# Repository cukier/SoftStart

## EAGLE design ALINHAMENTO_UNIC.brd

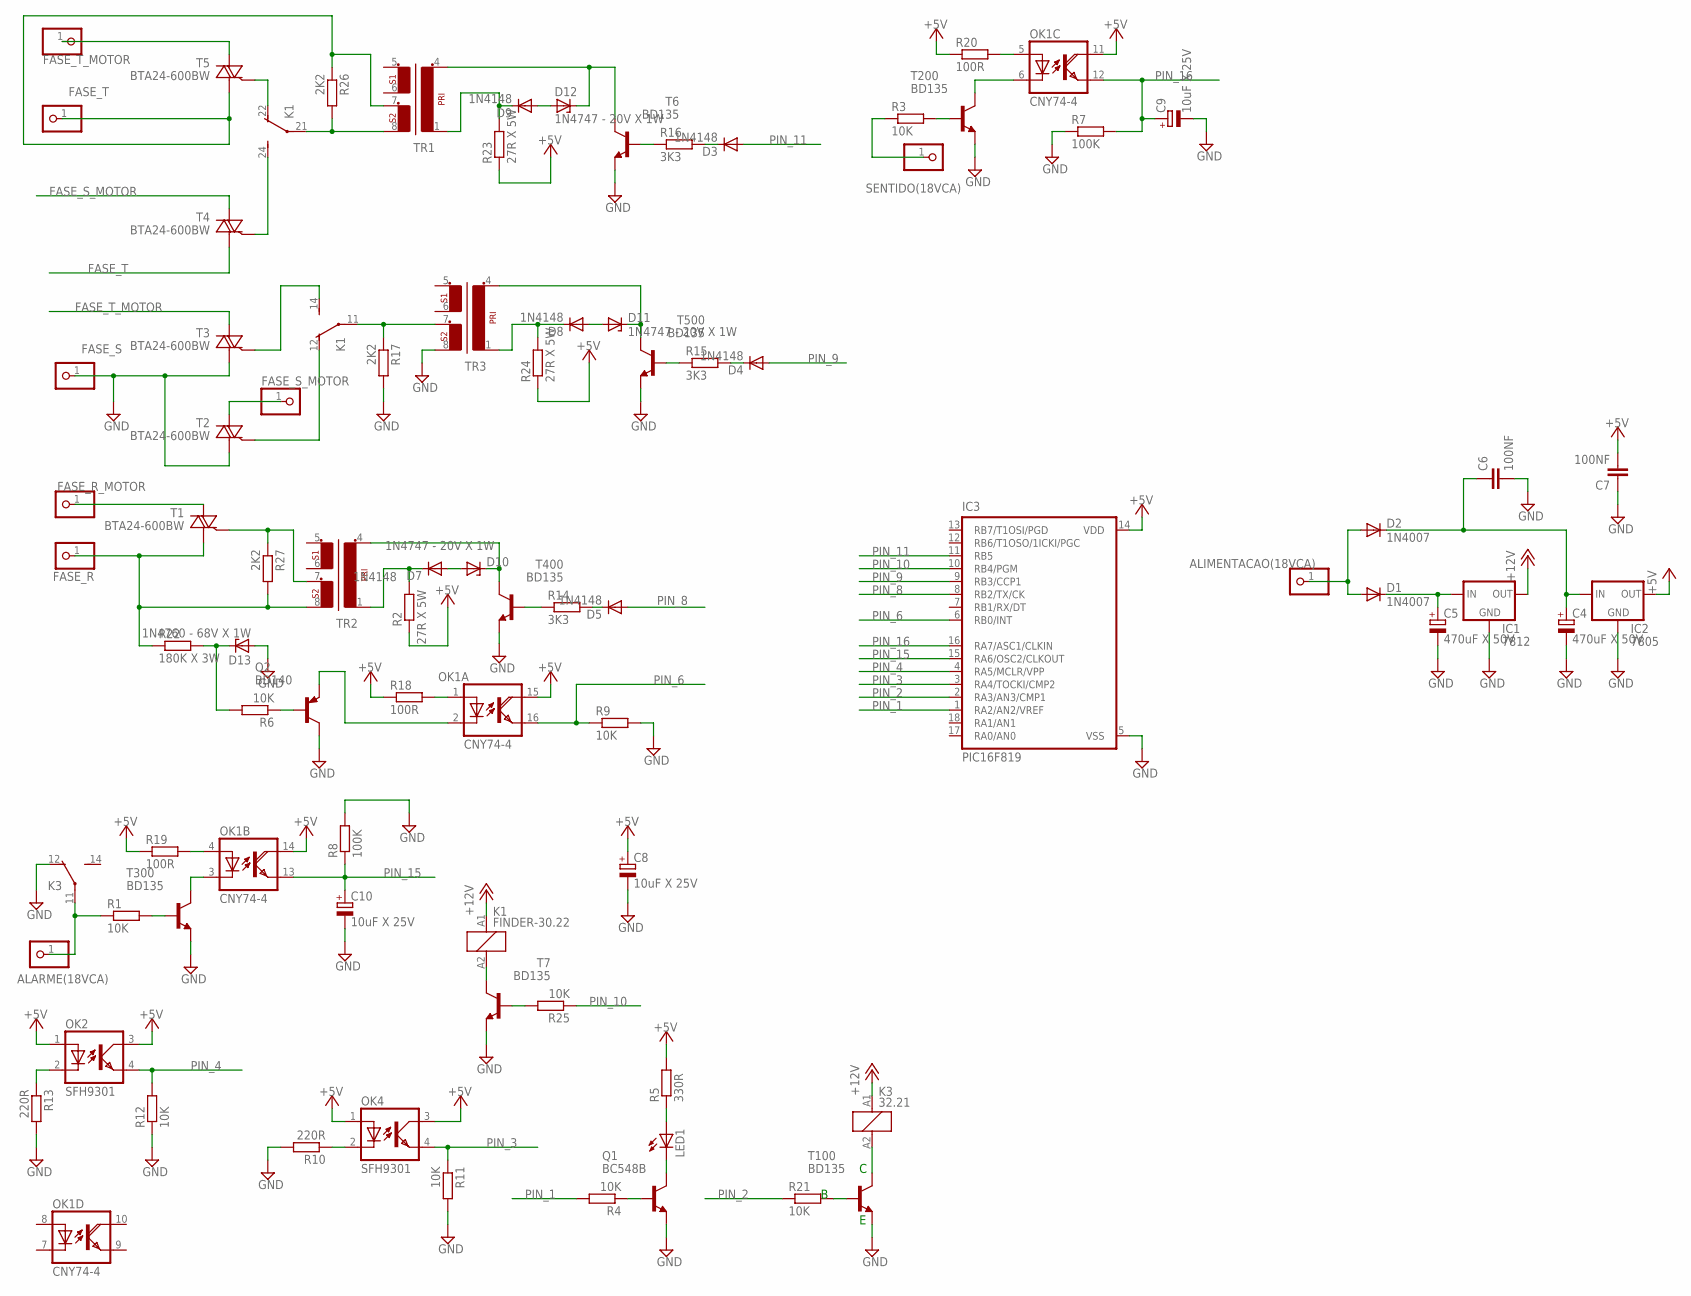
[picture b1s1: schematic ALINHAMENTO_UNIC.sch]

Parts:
ALARME(18VCA): PINHD-1X1; 1X01
ALIMENTACAO(18VCA): PINHD-1X1; 1X01
C4, C5: 470uF X 50V; E5-13
C6, C7: 100NF; C050-025X075
C8, C9, C10: 10uF X 25V; E2-5
D1, D2: 1N4007; DO41-10
D3, D4, D5, D7, D8, D9: 1N4148; DO35-10
D10, D11, D12: 1N4747 - 20V X 1W; DO41Z10
D13: 1N4760 - 68V X 1W; DO41Z10
FASE_R: PINHD-1X1; 1X01
FASE_R_MOTOR: PINHD-1X1; 1X01
FASE_S: PINHD-1X1; 1X01
FASE_S_MOTOR: PINHD-1X1; 1X01
FASE_T: PINHD-1X1; 1X01
FASE_T_MOTOR: PINHD-1X1; 1X01
IC1: 7812; 78MXXS
IC2: 7805; 78MXXS
IC3: PIC16F819; DIL18
K1: FINDER-30.22
K3: 32.21; RP51
LED1: LED5MM
OK1: CNY74-4; DIL16
OK2, OK4: SFH9301
Q1: BC548B; TO92-EBC
Q2: BD140; TO126
R1, R3, R4, R6, R9, R11, R12, R21, R25: 10K; 0207/10
R2, R23, R24: 27R X 5W; 0617/22
R5: 330R; 0207/10
R7, R8: 100K; 0207/10
R10, R13: 220R; 0207/10
R14, R15, R16: 3K3; 0207/10
R17, R26, R27: 2K2; 0207/10
R18, R19, R20: 100R; 0207/10
R22: 180K X 3W; 0617/22
SENTIDO(18VCA): PINHD-1X1; 1X01
T1, T2, T3, T4, T5: BTA24-600BW; TOP3S-1
T6, T7, T100, T200, T300, T400, T500: BD135; TO126
TR1, TR2, TR3: EE20-2

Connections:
+5V: C7.2, C8.+, IC2.OUT, IC3.14 (VDD), OK1.11 (COL), OK1.14 (COL), OK1.15 (COL), OK2.1 (A), OK2.3 (COL), OK4.1 (A), OK4.3 (COL), R2.1, R5.2, R18.1, R19.1, R20.1, R23.1, R24.1
+12V: IC1.OUT, K1.A1 (1), K3.A1 (1)
FASE_S_MOTOR: FASE_S_MOTOR.1, T2.A2, T4.A2
FASE_T: FASE_T.1, R26.1, T4.A1, T5.A1, TR1.7 (5)
FASE_T_MOTOR: FASE_T_MOTOR.1, T3.A2, T5.A2
GND: C4.-, C5.-, C6.2, C7.1, C8.-, C9.-, C10.-, D13.A, FASE_S.1, IC1.GND, IC2.GND, IC3.5 (VSS), K3.12 (O), Q1.E, Q2.2 (C), R7.1, R8.2, R9.2, R10.2, R11.2, R12.1, R13.2, R17.2, T2.A1, T3.A1, T6.1 (E), T7.1 (E), T100.1 (E), T200.1 (E), T300.1 (E), T400.1 (E), T500.1 (E), TR3.8 (6)
unnamed: OK4.2 (C), R10.1
unnamed: OK2.2 (C), R13.1
unnamed: ALIMENTACAO(18VCA).1, D1.A, D2.A
unnamed: C5.+, D1.C, IC1.IN
unnamed: R27.1, T1.G, TR2.7 (5)
unnamed: C4.+, C6.1, D2.C, IC2.IN
unnamed: Q1.B, R4.1
unnamed: K3.A2 (2), T100.2 (C)
unnamed: R25.2, T7.3 (B)
unnamed: LED1.A, R5.1
unnamed: OK1.1 (A), R18.2
unnamed: K1.A2 (2), T7.2 (C)
unnamed: D5.C, R14.2
unnamed: D9.A, D12.A
unnamed: FASE_R_MOTOR.1, T1.A2
unnamed: D4.C, R15.2
unnamed: D3.C, R16.2
unnamed: OK1.2 (C), Q2.1 (E)
unnamed: Q2.3 (B), R6.1
unnamed: FASE_R.1, R22.1, R27.2, T1.A1, TR2.8 (6)
unnamed: D8.A, D11.A
unnamed: D7.A, D10.A
unnamed: K1.21, R26.2, TR1.8 (6)
unnamed: K1.22 (O), T5.G
unnamed: ALARME(18VCA).1, K3.11, R1.1
unnamed: K1.24 (S), T4.G
unnamed: K1.11, R17.1, TR3.7 (5)
unnamed: K1.12 (O), T2.G
unnamed: K1.14 (S), T3.G
unnamed: R3.1, SENTIDO(18VCA).1
unnamed: R3.2, T200.3 (B)
unnamed: OK1.6 (C), T200.2 (C)
unnamed: OK1.5 (A), R20.2
unnamed: D13.C, R6.2, R22.2
unnamed: R1.2, T300.3 (B)
unnamed: OK1.3 (C), T300.2 (C)
unnamed: OK1.4 (A), R19.2
unnamed: R21.2, T100.3 (B)
unnamed: LED1.K (C), Q1.C
unnamed: R14.1, T400.3 (B)
unnamed: R15.1, T500.3 (B)
unnamed: R16.1, T6.3 (B)
unnamed: D12.C, T6.2 (C), TR1.4 (2)
unnamed: D11.C, T500.2 (C), TR3.4 (2)
unnamed: D9.C, R23.2, TR1.1
unnamed: D10.C, T400.2 (C), TR2.4 (2)
unnamed: D8.C, R24.2, TR3.1
unnamed: D7.C, R2.2, TR2.1
PIN_1: IC3.1 (RA2/AN2/VREF), R4.2
PIN_2: IC3.2 (RA3/AN3/CMP1), R21.1
PIN_3: IC3.3 (RA4/TOCKI/CMP2), OK4.4 (EMIT), R11.1
PIN_4: IC3.4 (RA5/MCLR/VPP), OK2.4 (EMIT), R12.2
PIN_6: IC3.6 (RB0/INT), OK1.16 (EMI), R9.1
PIN_8: D5.A, IC3.8 (RB2/TX/CK)
PIN_9: D4.A, IC3.9 (RB3/CCP1)
PIN_10: IC3.10 (RB4/PGM), R25.1
PIN_11: D3.A, IC3.11 (RB5)
PIN_15: C10.+, IC3.15 (RA6/OSC2/CLKOUT), OK1.13 (EMI), R8.1
PIN_16: C9.+, IC3.16 (RA7/ASC1/CLKIN), OK1.12 (EMI), R7.2

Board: 2 copper layers, 81 parts (0 on the bottom side), 65 nets, no tracks yet.

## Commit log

2013-02-07 primeiro
2013-02-07 simulacoes completas
2013-02-18 funcionando disparo para os dois lados da senoide
2013-02-21 funcionando ramapa
2013-02-26 teste bancada
